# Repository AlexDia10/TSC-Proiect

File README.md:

# TSC-Proiect

## Schema Bloc

## Bill Of Materials

| Parts                                 | Qty | CHECK_PRICE                                                                                                 | DATASHEET                                   |
|---------------------------------------|-----|--------------------------------------------------------------------------------------------------------------|---------------------------------------------|
| CHG_LED                               | 1   |                                                                                                              |                                             |
| R1_PINH1, R2_PINH1                    | 2   |                                                                                                              |                                             |
| S1                                    | 1   |                                                                                                              |                                             |
| EPD_C5                                | 1   |                                                                                                              |                                             |
| R3                                    | 1   |                                                                                                              |                                             |
| R1_PWRUSB                             | 1   |                                                                                                              |                                             |
| C1, C2, C4_USB, C6, C8, C9, C10, C6_DELAY | 8 |                                                                                                              |                                             |
| C3                                    | 1   |                                                                                                              |                                             |
| R4-R10, R_BOOT, R_CHANGE, R_C1, R_RESET| 11  |                                                                                                              |                                             |
| C7                                    | 1   |                                                                                                              |                                             |
| J4                                    | 1   |                                                                                                              |                                             |
| R_CAPACITOR                           | 1   |                                                                                                              |                                             |
| C5                                    | 1   |                                                                                                              |                                             |
| EPD_C1–EPD_C12                         | 9   |                                                                                                              |                                             |
| R2                                    | 1   |                                                                                                              |                                             |
| R1_BAT                                | 1   |                                                                                                              |                                             |
| Q1, Q2                                | 2   |                                                                                                              |                                             |
| R2_BAT                                | 1   |                                                                                                              |                                             |
| C5_USB                                | 1   |                                                                                                              |                                             |
| C1_BAT, C2_BAT                        | 4   |                                                                                                              |                                             |
| C4                                    | 1   |                                                                                                              |                                             |
| R2-USB, R2-USB1                       | 2   |                                                                                                              |                                             |
| L1                                    | 1   |                                                                                                              |                                             |
| IC1                                   | 1   |                                                                                                              |                                             |
| BOOT_BUTTON, CHANGE_BUTTON, RESET_BUTTON | 3 |                                                                                                              |                                             |
| C10_SUPERCAP                          | 1   | [SnapEDA](https://www.snapeda.com/parts/PC5H225/Vishay/view-part/?ref=eda)                                   |                                             |
| U3                                    | 1   | [SnapEDA](https://www.snapeda.com/parts/DS3231SN%23/Analog+Devices/view-part/?ref=eda)                      |                                             |
| U2                                    | 1   | [SnapEDA](https://www.snapeda.com/parts/ESP32-C6-WROOM-1-N8/Espressif+Systems/view-part/?ref=eda)           |                                             |
| PFMF.050.1                            | 1   |                                                                                                              | [Datasheet](http://datasheets.avx.com/schottky.pdf) |
| D2, D7                                | 2   |                                                                                                              |                                             |
| SENSOR2                               | 1   |                                                                                                              |                                             |
| MCP73831                              | 1   |                                                                                                              |                                             |
| J1                                    | 1   | [SnapEDA](https://www.snapeda.com/parts/MAX17048GT10/Analog+Devices/view-part/?ref=eda)                     |                                             |
| U4                                    | 1   | [SnapEDA](https://www.snapeda.com/parts/MBR0530/Onsemi/view-part/?ref=eda)                                  |                                             |
| D3, D4, D5                            | 3   | [SnapEDA](https://www.snapeda.com/parts/PG81010603MR/Littelfuse/view-part/?ref=eda)                         |                                             |
| D6, D8–D12                            | 6   |                                                                                                              |                                             |
| J3                                    | 1   |                                                                                                              |                                             |
| J2                                    | 1   | [SnapEDA](https://www.snapeda.com/parts/SI1308EDL-T1-GE3/Vishay+Siliconix/view-part/?ref=eda)               |                                             |
| Q3                                    | 1   |                                                                                                              |                                             |
| TP1–TP17                              | 17  |                                                                                                              |                                             |
| D1                                    | 1   | [SnapEDA](https://www.snapeda.com/parts/USBLC6-2SC6Y/STMicroelectronics/view-part/?ref=eda)                 |                                             |
| U1                                    | 1   | [SnapEDA](https://www.snapeda.com/parts/W25Q512JV/Winbond+Electronics/view-part/?ref=eda)                   |                                             |
| IC4                                  |     |                                                                                                              |                                             |

## Specificații Hardware

**🔹 1. Microcontroller – ESP32-C6-WROOM-1-N8**

**CPU:** RISC-V 32-bit, 160 MHz (single-core)

**Memorie:** 320KB SRAM, 512KB ROM, 8MB Flash SPI (W25Q512JVEIQ)

**Conectivitate:** Wi-Fi 6 (300 Mbps), Bluetooth 5 LE (Mesh), Zigbee 3.0

**Periferice:** 4×SPI, 2×I²C, 2×UART, USB 2.0 OTG

**Consum:** 80 mA activ, 1.5 mA sleep, 20 µA deep sleep

**Wake-up:** GPIO, RTC, UART, senzor BME680

**🔹 2. Alimentare**

**Încărcare:** MCP73831 (100–500 mA), LED stare (GPIO18)

**LDO:** BD5229G-TR (eficiență 92%, ripple <50mV)

**Fuel Gauge:** MAX17048 (±1% SOC, alertă critică, 7 µA consum)

**🔹 3. Senzori**

**BME680 (I²C, 0x76):** temp., umiditate, presiune, VOC/eCO₂

Algoritm IAQ (BSEC), compensare termică, calibrare din fabrică

**RTC – DS3231SN#:** ±2ppm, backup cu supercondensator, alarmă, square wave

**🔹 4. Afișaj E-Ink** – 7.5", 800×480 px

**Interfață:** SPI + CS/DC/RST/BUSY

**Consum:** 15–25 mA la refresh, 0 mA static

**Avantaj:** imagine persistentă fără consum

**🔹 5. Interfețe & Stocare**

**USB-C:** alimentare, serial console, DFU update (ESD + Polyfuse 500 mA)

**Qwiic I²C:** extensii senzori/modul

**MicroSD:** loguri/fișiere, SPI/SD

**Flash externă:** W25Q512JVEIQ (quad SPI, aplicații mari)

**🔹 6. Interacțiune**

**Butoane:** 3× tactile (navigare/selectare/back), debouncing HW/SW

**🔹 7. Interfețe Utilizate**

Interfață	Componente
SPI	E-Ink, Flash, SD Card
I²C	BME680, MAX17048, DS3231, Qwiic
GPIO	Butoane, control display
USB	Alimentare, date

## Alocarea pinilor pentru ESP32-C6

| Pin ESP32-C6 | Componentă / Semnal           | Descriere                                                                 |
|--------------|-------------------------------|---------------------------------------------------------------------------|
| GPIO1        | I²C SDA (BME680, MAX17048, DS3231, Qwiic) | Linie de date partajată pentru toți senzorii și RTC-ul conectați la magistrala I²C. |
| GPIO2        | I²C SCL (BME680, MAX17048, DS3231, Qwiic) | Linie de clock utilizată pentru sincronizarea comunicației I²C.          |
| GPIO5        | SPI MISO (E-Paper)            | Primește date de la afișajul E-Paper prin interfața SPI.                 |
| GPIO6        | SPI MOSI (E-Paper)            | Trimite date către afișajul E-Paper prin interfața SPI.                 |
| GPIO7        | SPI CLK (E-Paper)             | Semnal de clock pentru sincronizarea comunicației SPI cu afișajul.      |
| GPIO8        | SPI CS (E-Paper)              | Semnal Chip Select pentru activarea afișajului E-Paper.                 |
| GPIO9        | E-Paper DC (Data/Command)     | Selectează între trimiterea de date sau comenzi către afișaj.           |
| GPIO10       | E-Paper RST                   | Reset hardware pentru afișajul E-Paper.                                 |
| GPIO11       | E-Paper BUSY                  | Indică dacă afișajul este ocupat și nu poate primi comenzi.             |
| GPIO12       | Button #1                     | Buton de control, ex: „Pagina următoare”.                                |
| GPIO13       | Button #2                     | Buton de control, ex: „Pagina anterioară”.                               |
| GPIO14       | Button #3                     | Buton de control, ex: „Meniu” sau „Selectare”.                           |
| GPIO15       | MAX17048 ALERT (opțional)     | Semnal de alertă de la senzorul de baterie (ex: baterie descărcată).    |
| GPIO16       | USB D+ (intern la USB PHY)    | Linie de semnal diferențial pozitiv pentru conexiunea USB 2.0.          |
| GPIO17       | USB D- (intern la USB PHY)    | Linie de semnal diferențial negativ pentru conexiunea USB 2.0.          |
| GPIO18       | LED de status (opțional)      | LED pentru indicarea stărilor (Wi-Fi, încărcare etc.).                  |
| GPIO19       | SD Card CS (opțional)         | Semnal Chip Select pentru cardul microSD.                                |
| GPIO20       | SD Card MISO (opțional)       | Linie de recepție a datelor de la cardul microSD.                       |
| GPIO21       | SD Card MOSI (opțional)       | Linie de transmisie a datelor către cardul microSD.                     |
| GPIO4        | SD Card CLK (opțional)        | Semnal de clock pentru comunicația SPI cu cardul microSD.               |

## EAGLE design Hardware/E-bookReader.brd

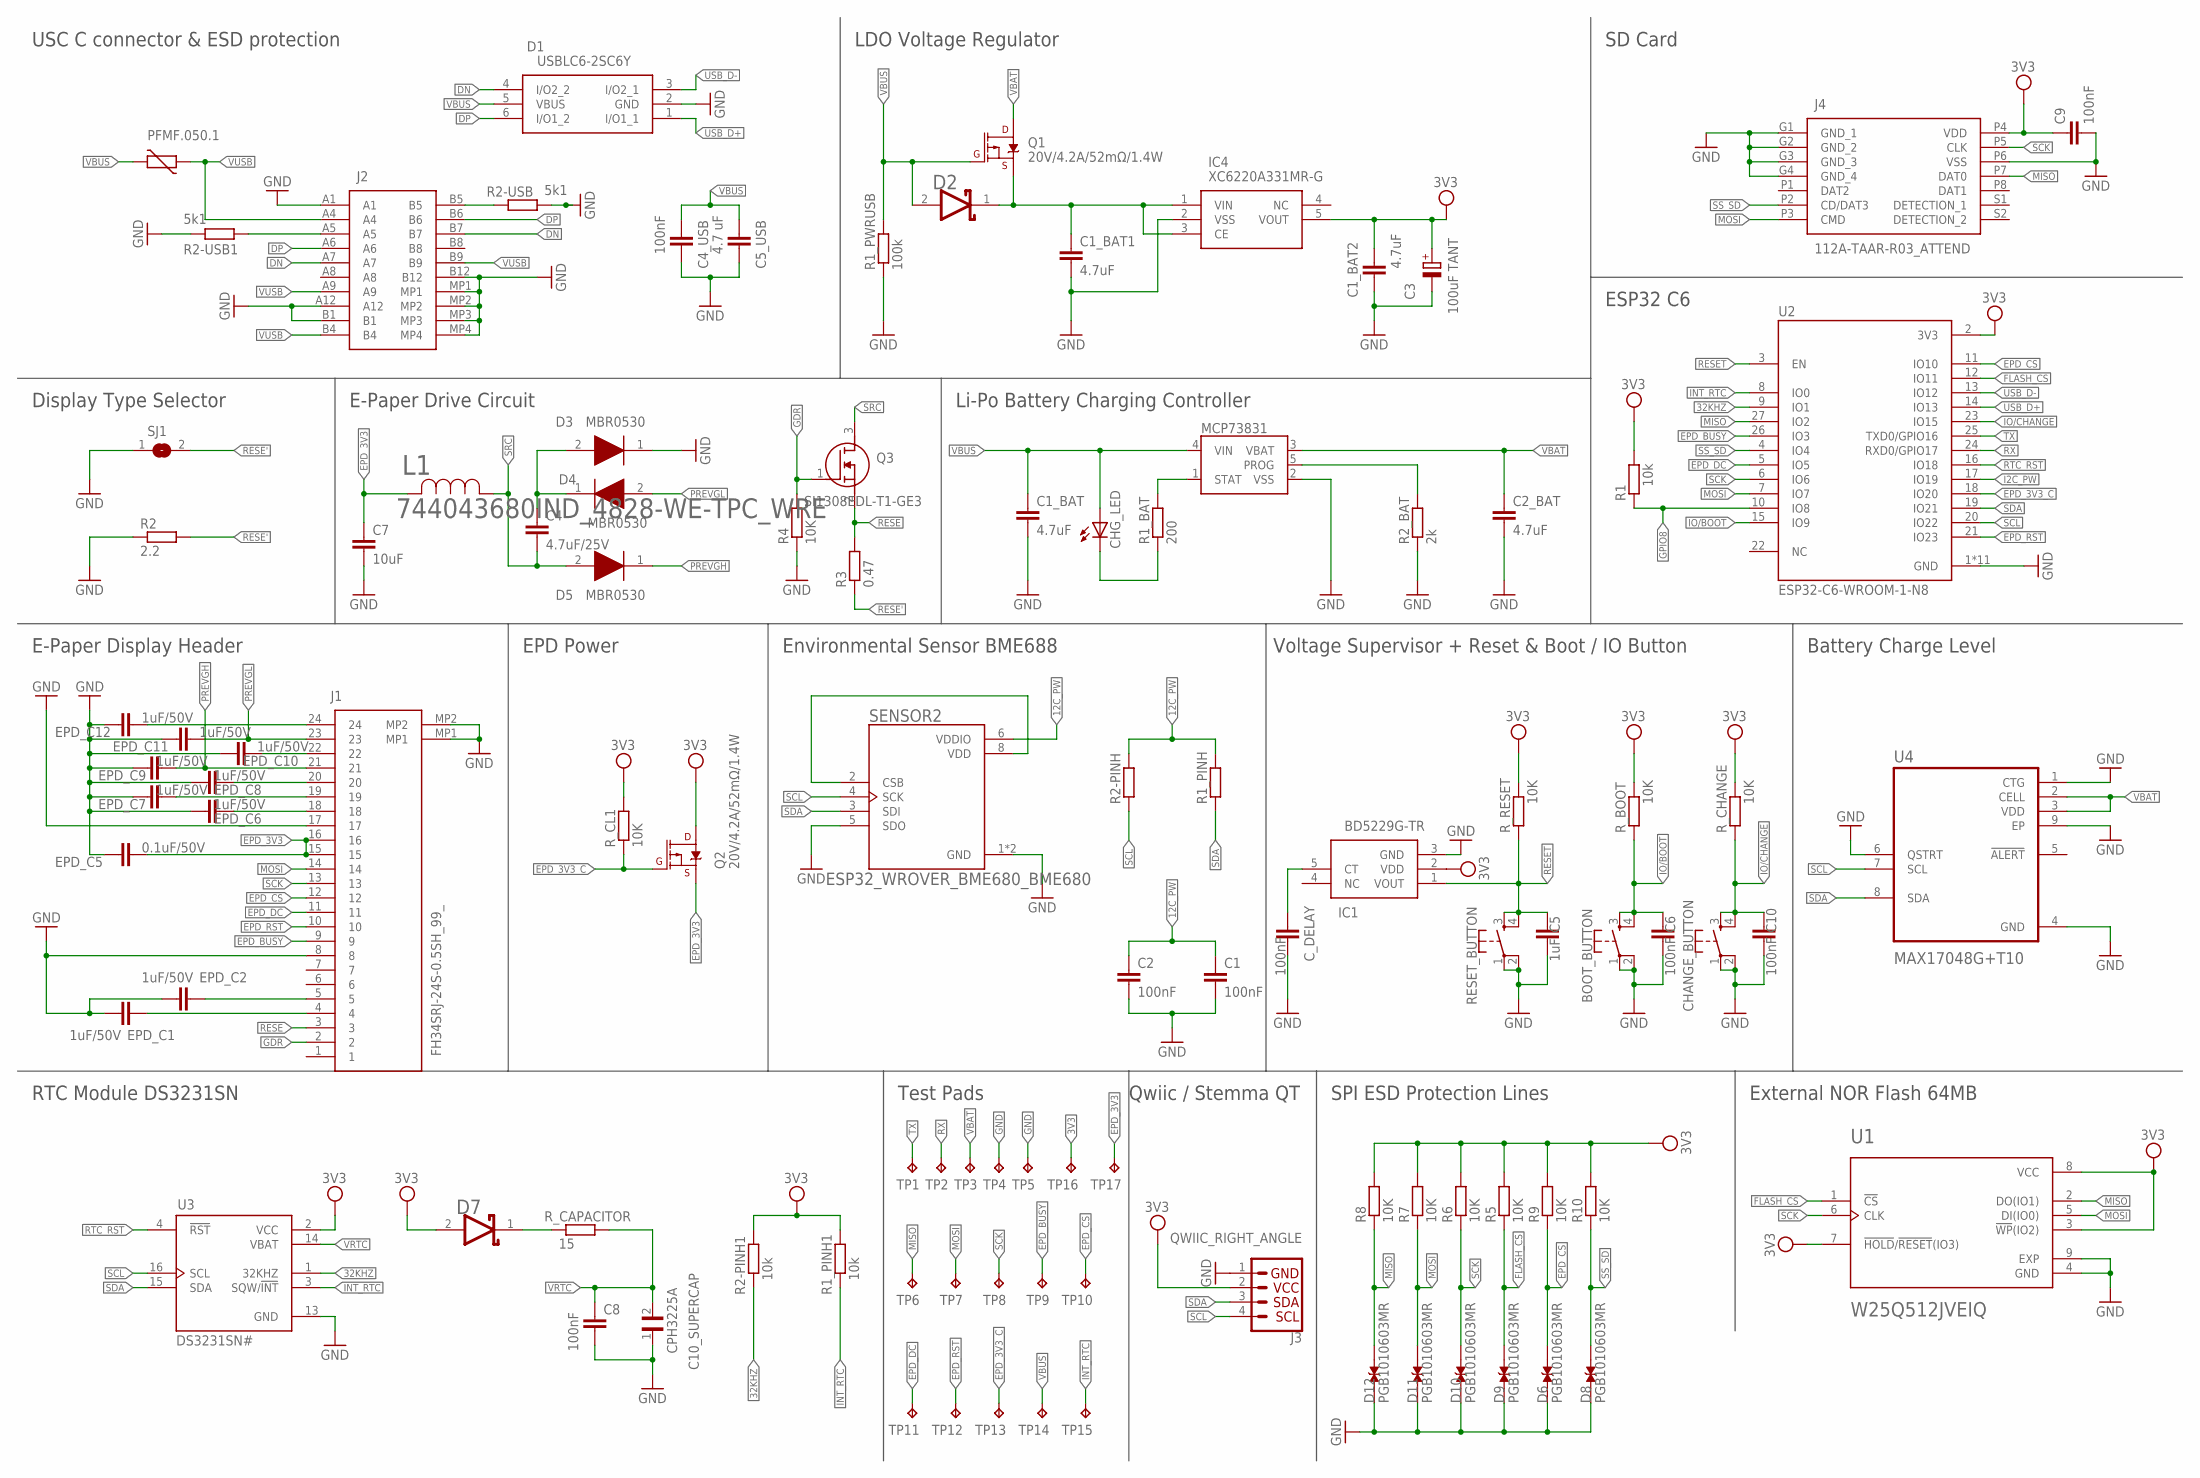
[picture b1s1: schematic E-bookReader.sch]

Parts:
BOOT_BUTTON: BUTTON_CUSYOMV1; MYBUTTON
C1, C2, C4_USB, C6, C8, C9, C10: 100nF; EAGLE-LTSPICE_C0402
C1_BAT, C1_BAT1, C1_BAT2, C2_BAT: 4.7uF; EAGLE-LTSPICE_C0402
C3: 100uF TANT; RCL_CT3528
C4: 4.7uF/25V; EAGLE-LTSPICE_C0402
C5: 1uF; EAGLE-LTSPICE_C0402
C5_USB: 4.7 uF; EAGLE-LTSPICE_C0402
C7: 10uF; EAGLE-LTSPICE_C0402
C10_SUPERCAP: CPH3225A; CAPCP3225X100N
CHANGE_BUTTON: BUTTON_CUSYOMV1; MYBUTTON
CHG_LED: ADAFRUIT_LEDCHIP-LED0603; ADAFRUIT_CHIP-LED0603
C_DELAY: 100nF; EAGLE-LTSPICE_C0402
D1: USBLC6-2SC6Y; SOT95P280X145-6N
D2, D7: ESP32_WROVER_AVX---SD0805S020S1R0_AVX_SD0805S020S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; ESP32_WROVER_AVX---SD0805S020S1R0_AVX_SD0805S020S1R0_0
D3, D4, D5: MBR0530; SOD3716X135N
D6, D8, D9, D10, D11, D12: PGB1010603MR; DIOC1608X36N
EPD_C1, EPD_C2, EPD_C6, EPD_C7, EPD_C8, EPD_C9, EPD_C10, EPD_C11, EPD_C12: 1uF/50V; EAGLE-LTSPICE_C0402
EPD_C5: 0.1uF/50V; EAGLE-LTSPICE_C0402
IC1: BD5229G-TR; SOT95P280X125-5N
IC4: XC6220A331MR-G; SOT95P280X120-5N
J1: FH34SRJ-24S-0.5SH_99_; FH34SRJ24S05SH99
J2: SAMACSYS_PARTS_USB4110-GF-A; SAMACSYS_PARTS_USB4110GFA
J3: QWIIC_RIGHT_ANGLE; JST04_1MM_RA
J4: 112A-TAAR-R03_ATTEND; 112ATAARR03ATTEND
L1: 744043680IND_4828-WE-TPC_WRE; IND_4828-WE-TPC_WRE
MCP73831: ESP32_WROVER_SPARKFUN-IC-POWER_MCP73831; ESP32_WROVER_SPARKFUN-IC-POWER_SOT23-5
PFMF.050.1: ESP32C6_VARISTORCN1812; ESP32C6_VARISTOR_CT/CN1812
Q1, Q2: 20V/4.2A/52mΩ/1.4W; ESP32_WROVER_SPARKFUN-DISCRETESEMI_SOT23-3
Q3: SI1308EDL-T1-GE3; SOT65P210X110-3N
R1, R1_PINH1, R2-PINH1: 10k; ESP32_WROVER_EAGLE-LTSPICE_R0402
R1_BAT: 200; ESP32_WROVER_EAGLE-LTSPICE_R0402
R1_PINH, R2-PINH: ESP32_WROVER_EAGLE-LTSPICE_RR0402; ESP32_WROVER_EAGLE-LTSPICE_R0402
R1_PWRUSB: 100k; ESP32_WROVER_EAGLE-LTSPICE_R0402
R2: 2.2; ESP32_WROVER_EAGLE-LTSPICE_R0402
R2-USB, R2-USB1: 5k1; ESP32_WROVER_EAGLE-LTSPICE_R0402
R2_BAT: 2k; ESP32_WROVER_EAGLE-LTSPICE_R0402
R3: 0.47; ESP32_WROVER_EAGLE-LTSPICE_R0402
R4, R5, R6, R7, R8, R9, R10: 10K; ESP32_WROVER_EAGLE-LTSPICE_R0402
RESET_BUTTON: BUTTON_CUSYOMV1; MYBUTTON
R_BOOT: 10K; ESP32_WROVER_EAGLE-LTSPICE_R0402
R_CAPACITOR: 15; ESP32_WROVER_EAGLE-LTSPICE_R0402
R_CHANGE: 10K; ESP32_WROVER_EAGLE-LTSPICE_R0402
R_CL1: 10K; ESP32_WROVER_EAGLE-LTSPICE_R0402
R_RESET: 10K; ESP32_WROVER_EAGLE-LTSPICE_R0402
SENSOR2: ESP32_WROVER_BME680_BME680; ESP32_WROVER_BME680_PSON80P300X300X100-8N
SJ1: SJ
TP1, TP2, TP3, TP4, TP5, TP6, TP7, TP8, TP9, TP10, TP11, TP12, TP13, TP14, TP15, TP16, TP17: TPTP20R; TP20R
U1: W25Q512JVEIQ; SON127P600X800X80-9N
U2: ESP32-C6-WROOM-1-N8; XCVR_ESP32-C6-WROOM-1-N8
U3: DS3231SN#; SOIC127P1032X265-16N
U4: MAX17048G+T10; SON50P200X200X80-9N

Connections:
3V3: C1_BAT2.1, C3.+, C9.1, D7.2 (ANODE), IC1.2 (VDD), IC4.5 (VOUT), J3.2, J4.P4 (VDD), Q2.3 (D), R1.2, R1_PINH1.2, R2-PINH1.2, R5.2, R6.2, R7.2, R8.2, R9.2, R10.2, R_BOOT.2, R_CHANGE.2, R_CL1.2, R_RESET.2, TP16.TP, U1.3 (!WP!(IO2)), U1.7 (!HOLD!/!RESET!(IO3)), U1.8 (VCC), U2.2 (3V3), U3.2 (VCC)
12C_PW: C1.1, C2.1, R1_PINH.2, R2-PINH.2, SENSOR2.6 (VDDIO)
32KHZ: R2-PINH1.1, U2.9 (IO1), U3.1 (32KHZ)
DN: D1.4 (I/O2_2), J2.A7, J2.B7
DP: D1.6 (I/O1_2), J2.A6, J2.B6
EPD_3V3: C7.1, EPD_C5.1, J1.15, J1.16, L1.2, Q2.2 (S), TP17.TP
EPD_3V3_C: Q2.1 (G), R_CL1.1, TP13.TP, U2.18 (IO20)
EPD_BUSY: J1.9, TP9.TP, U2.26 (IO3)
EPD_CS: D6.2, J1.12, R9.1, TP10.TP, U2.11 (IO10)
EPD_DC: J1.11, TP11.TP, U2.5 (IO5)
EPD_RST: J1.10, TP12.TP, U2.21 (IO23)
FLASH_CS: D9.2, R5.1, U1.1 (!CS), U2.12 (IO11)
GDR: J1.2, Q3.1 (G), R4.2
GND: BOOT_BUTTON.1, BOOT_BUTTON.2, C1.2, C1_BAT.2, C1_BAT1.2, C1_BAT2.2, C2.2, C2_BAT.2, C3.-, C4_USB.2, C5.2, C5_USB.2, C6.2, C7.2, C8.2, C9.2, C10.2, C10_SUPERCAP.1, CHANGE_BUTTON.1, CHANGE_BUTTON.2, C_DELAY.2, D1.2 (GND), D3.1 (K), D6.1, D8.1, D9.1, D10.1, D11.1, D12.1, EPD_C1.2, EPD_C2.2, EPD_C5.2, EPD_C6.2, EPD_C7.2, EPD_C8.2, EPD_C9.2, EPD_C10.2, EPD_C11.2, EPD_C12.2, IC1.3 (GND), IC4.2 (VSS), J1.8, J1.17, J1.MP1, J1.MP2, J2.A1, J2.A12, J2.B1, J2.B12, J2.MP1, J2.MP2, J2.MP3, J2.MP4, J3.1, J4.G1 (GND_1), J4.G2 (GND_2), J4.G3 (GND_3), J4.G4 (GND_4), J4.P6 (VSS), MCP73831.2 (VSS), R1_PWRUSB.1, R2.1, R2-USB.2, R2-USB1.1, R2_BAT.1, R4.1, RESET_BUTTON.1, RESET_BUTTON.2, SENSOR2.1 (GND), SENSOR2.5 (SDO), SENSOR2.7 (GND), SJ1.1, TP4.TP, TP5.TP, U1.4 (GND), U1.9 (EXP), U2.1 (GND), U2.28 (GND), U2.29_1 (GND), U2.29_2 (GND), U2.29_3 (GND), U2.29_4 (GND), U2.29_5 (GND), U2.29_6 (GND), U2.29_7 (GND), U2.29_8 (GND), U2.29_9 (GND), U3.13 (GND), U4.1 (CTG), U4.4 (GND), U4.6 (QSTRT), U4.9 (EP)
GPIO8: R1.1, U2.10 (IO8)
I2C_PW: U2.17 (IO19)
INT_RTC: R1_PINH1.1, TP15.TP, U2.8 (IO0), U3.3 (SQW/!INT)
IO/BOOT: BOOT_BUTTON.3, BOOT_BUTTON.4, C6.1, R_BOOT.1, U2.15 (IO9)
IO/CHANGE: C10.1, CHANGE_BUTTON.3, CHANGE_BUTTON.4, R_CHANGE.1, U2.23 (IO15)
MISO: D12.2, J4.P7 (DAT0), R8.1, TP6.TP, U1.2 (DO(IO1)), U2.27 (IO2)
MOSI: D11.2, J1.14, J4.P3 (CMD), R7.1, TP7.TP, U1.5 (DI(IO0)), U2.7 (IO7)
unnamed: C1_BAT1.1, D2.1 (CATHODE), IC4.1 (VIN), IC4.3 (CE), Q1.2 (S)
unnamed: EPD_C12.1, J1.24
unnamed: J2.A5, R2-USB1.2
unnamed: C4.1, D3.2 (A), D4.1 (K)
unnamed: CHG_LED.C, R1_BAT.1
unnamed: MCP73831.1 (STAT), R1_BAT.2
unnamed: MCP73831.5 (PROG), R2_BAT.2
unnamed: J2.B5, R2-USB.1
unnamed: C_DELAY.1, IC1.5 (CT)
unnamed: EPD_C2.1, J1.5
unnamed: D7.1 (CATHODE), R_CAPACITOR.1
unnamed: EPD_C10.1, J1.22
unnamed: EPD_C1.1, J1.4
unnamed: EPD_C8.1, J1.20
unnamed: SENSOR2.2 (CSB), SENSOR2.8 (VDD)
unnamed: EPD_C7.1, J1.19
unnamed: EPD_C6.1, J1.18
PREVGH: D5.1 (K), EPD_C9.1, J1.21
PREVGL: D4.2 (A), EPD_C11.1, J1.23
RESE: J1.3, Q3.2 (S), R3.2
RESE': R2.2, R3.1, SJ1.2
RESET: C5.1, IC1.1 (VOUT), RESET_BUTTON.3, RESET_BUTTON.4, R_RESET.1, U2.3 (EN)
RTC_RST: U2.16 (IO18), U3.4 (!RST)
RX: TP2.TP, U2.24 (RXD0/GPIO17)
SCK: D10.2, J1.13, J4.P5 (CLK), R6.1, TP8.TP, U1.6 (CLK), U2.6 (IO6)
SCL: J3.4, R2-PINH.1, SENSOR2.4 (SCK), U2.20 (IO22), U3.16 (SCL), U4.7 (SCL)
SDA: J3.3, R1_PINH.1, SENSOR2.3 (SDI), U2.19 (IO21), U3.15 (SDA), U4.8 (SDA)
SRC: C4.2, D5.2 (A), L1.1, Q3.3 (D)
SS_SD: D8.2, J4.P2 (CD/DAT3), R10.1, U2.4 (IO4)
TX: TP1.TP, U2.25 (TXD0/GPIO16)
USB_D+: D1.1 (I/O1_1), U2.14 (IO13)
USB_D-: D1.3 (I/O2_1), U2.13 (IO12)
VBAT: C2_BAT.1, MCP73831.3 (VBAT), Q1.3 (D), TP3.TP, U4.2 (CELL), U4.3 (VDD)
VBUS: C1_BAT.1, C4_USB.1, C5_USB.1, CHG_LED.A, D1.5 (VBUS), D2.2 (ANODE), MCP73831.4 (VIN), PFMF.050.1.2, Q1.1 (G), R1_PWRUSB.2, TP14.TP
VRTC: C8.1, C10_SUPERCAP.2, R_CAPACITOR.2, U3.14 (VBAT)
VUSB: J2.A4, J2.A9, J2.B4, J2.B9, PFMF.050.1.1

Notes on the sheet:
USC C connector & ESD protection
LDO Voltage Regulator
SD Card
Display Type Selector
E-Paper Drive Circuit
Li-Po Battery Charging Controller
ESP32 C6
E-Paper Display Header
EPD Power
Environmental Sensor BME688
Voltage Supervisor + Reset & Boot / IO Button
Battery Charge Level
RTC Module DS3231SN
Test Pads
Qwiic / Stemma QT
SPI ESD Protection Lines
External NOR Flash 64MB

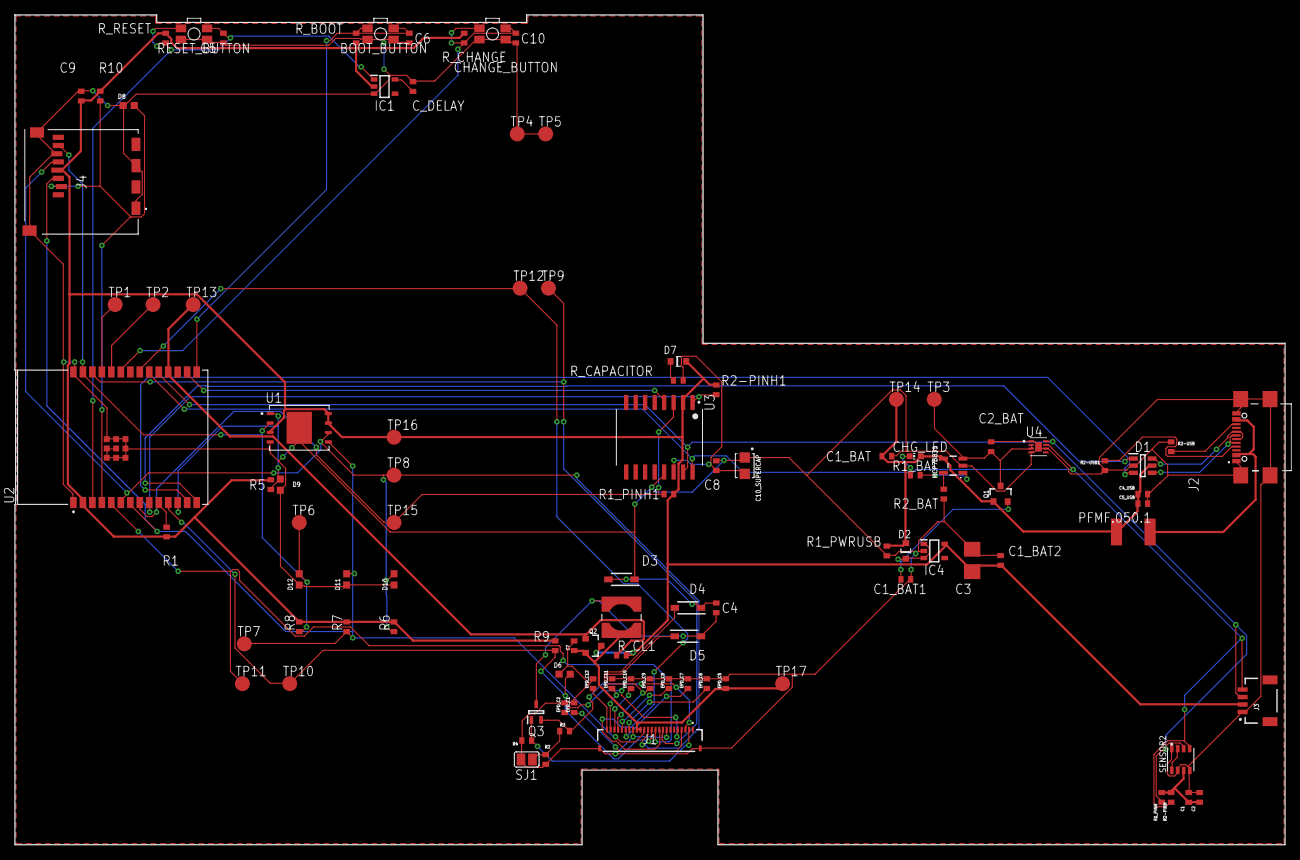
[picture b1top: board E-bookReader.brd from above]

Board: 2 copper layers, 170.2 x 111.2 mm, 103 parts (0 on the bottom side), 56 nets.

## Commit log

2025-04-06 Create LICENSE
2025-04-06 Hardware upload
2025-04-06 Images upload
2025-04-06 Manufacturing upload
2025-04-06 Mechanical upload

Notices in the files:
parts and their libraries:
COPYRIGHT: Copyright (C) 2024 Ultra Librarian. All rights reserved.
